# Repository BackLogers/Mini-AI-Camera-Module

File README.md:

# Mini AI Camera Module

## Project Description 

The **Mini AI Camera Module** is a compact platform based on the **ESP32-S3**, combining a standard visible-light camera with a **LiDAR** sensor. The module is designed as a low-cost solution for implementing simple AI algorithms, image recognition, and basic 3D depth perception.

This project includes:
- **OV5640** visible-light camera (5 MP)
- **VL53L5CX** LiDAR camera with an **8×8 pixel** depth map  

*(A future hardware revision is planned to include the **VL53L9CX** sensor featuring a 54×42 pixel resolution.)*

## Key Features

1. **Compact size: 25×25 mm**  
   The module includes mounting holes for easy installation, e.g., in mobile robots.

2. **Two complementary imaging systems**  
   - **OV5640 – 5 MP visible-light camera**  
   - **VL53L5CX – 8×8 pixel LiDAR sensor**

3. **Low production cost**  
   - Uses popular and cost-effective electronic components  
   - PCB designed with simple manufacturing requirements  
   - Complete **JLCPCB** production files included

4. **Ideal for autonomous and IoT projects**  
   Suitable for robotics, autonomous vehicles, perception systems, and IoT devices.

5. **Wireless connectivity**  
   With the ESP32-S3, the module supports:  
   - WiFi  
   - Bluetooth  
   - **ESP-NOW**

6. **Convenient USB and UART interfaces**  
   - Vertical **USB-C** port allows direct mounting to a robot chassis  
   - **SBU1 and SBU2** lines are exposed as **UART**, enabling easy integration with external devices

7. **Easy to use and based on open-source libraries**  
   The project is designed to be simple to integrate and develop with. It relies on well-maintained open-source libraries (including SparkFun drivers) as well as built-in components from the ESP-IDF framework.

8. **Open-source project (Apache 2.0 License)**  
   The entire project is fully open-source and released under the Apache 2.0 license, allowing both personal and commercial use with minimal restrictions.

## Repository Contents

- Technical documentation  
- Schematics and PCB design  
- JLCPCB fabrication files  
- Example firmware for **Arduino**

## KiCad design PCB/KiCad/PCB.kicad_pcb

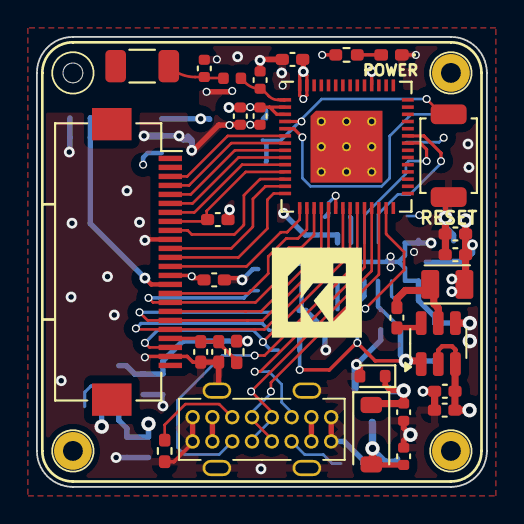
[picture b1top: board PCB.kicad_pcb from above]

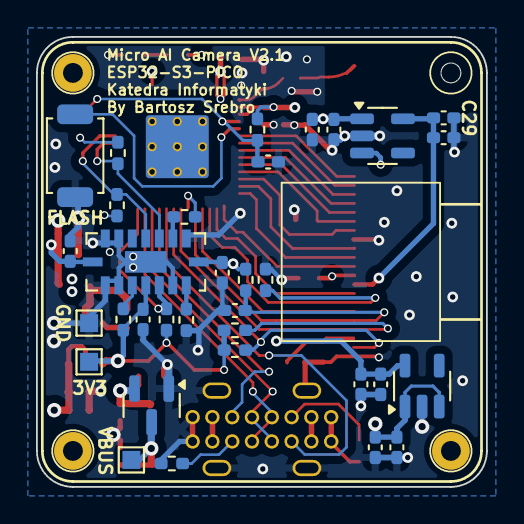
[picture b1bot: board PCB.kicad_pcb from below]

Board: 4 copper layers, 25.0 x 25.0 mm, 67 parts (33 on the bottom side), 42 nets.

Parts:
AE1: Antenna_Ceramic; C_1206_3216Metric
C1: NC; C_0402_1005Metric
C2: 4.7pF; C_0402_1005Metric
C3, C4, C18, C19, C27, C28, C33: 4.7uF; C_0402_1005Metric_Pad0.74x0.62mm_HandSolder
C5, C9, C12, C13, C26, C29, C30, C34, C35, C37: 100nF; C_0402_1005Metric_Pad0.74x0.62mm_HandSolder
C6: 1uF; C_0402_1005Metric
C7, C10: 22uF; C_0402_1005Metric
C8: 100nF; C_0402_1005Metric
C11: 1uF; C_0402_1005Metric_Pad0.74x0.62mm_HandSolder
C15, C21: 10uF; C_0402_1005Metric_Pad0.74x0.62mm_HandSolder
C31, C32: 22uF; C_0402_1005Metric_Pad0.74x0.62mm_HandSolder
C36: 15pF; C_0402_1005Metric_Pad0.74x0.62mm_HandSolder
D1: SBR3U40S1F-7; D_SOD-123
D2: ESD5Z5.0; D_SOD-523
D4: LED; LED_0402_1005Metric_Pad0.77x0.64mm_HandSolder
FB1: 120R-1.3A; R_0402_1005Metric_Pad0.72x0.64mm_HandSolder
H1: MountingHole; MountingHole_1.1mm_M1_No_Pad
H2, H3, H4: MountingHole; MountingHole_1.1mm_M1_DIN965_Pad
J1: USB_C_Vertical; USB_C_Hanbo Electronic MC-118LD-H65
J2: Conn_Camera; Hirose_FH12-24S-0.5SH_1x24-1MP_P0.50mm_Horizontal_WithCamer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
L1: 5.6nH/3.0nH; L_0402_1005Metric
L2: 4.7uF; L_2016
R1, R2, R3, R8: 47k; R_0402_1005Metric_Pad0.72x0.64mm_HandSolder
R4, R5, R10, R11, R15: 4.7k; R_0402_1005Metric_Pad0.72x0.64mm_HandSolder
R6, R7: 5.1k; R_0402_1005Metric_Pad0.72x0.64mm_HandSolder
R9, R12, R13: 10k; R_0402_1005Metric_Pad0.72x0.64mm_HandSolder
SW1: SW_Reset; SW_Push_3.0x4.0mm
SW2: SW_Flash; SW_Push_3.0x4.0mm
TP1: TestPoint_VIN; TestPoint_Pad_1.0x1.0mm
TP2: TestPoint_GND; TestPoint_Pad_1.0x1.0mm
TP3: TestPoint_3V3; TestPoint_Pad_1.0x1.0mm
U1: VL53L5CX-Sensor_Distance; ST_VL53L5CX_HandSoldering
U2: ESP32-S3FH4R2; QFN-56-1EP_7x7mm_P0.4mm_EP4x4mm_ThermalVias_ESP32
U3: CH213K; SOT-23
U5: RT9193-1V2; SOT-23-5
U6: RT9193-2V8; SOT-23-5
U7: AP63203WU; TSOT-23-6

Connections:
+1V2: C27.1, C29.1, J2.10, U5.5 (VOUT)
+2V8: C28.1, C30.1, FB1.1, U6.5 (VOUT)
+3V3: C3.2, C4.1, C5.1, C7.2, C8.1, C9.2, C31.2, C32.2, C35.2, J2.11, L2.2, R1.2, R2.2, R4.2, R5.2, R8.1, R9.1, R10.2, R11.2, R13.1, R15.1, TP3.1, U1.A4 (IOVDD), U1.B1 (AVDD), U1.B7 (AVDD), U2.2 (VDD3P3), U2.3 (VDD3P3), U2.20 (VDD3P3_RTC), U2.46 (VDD3P3_CPU), U2.55 (VDDA), U2.56 (VDDA), U7.1 (FB)
+5V: C10.2, C12.1, C13.1, C15.1, C18.1, C19.1, C21.1, D1.1 (K), D2.1 (K), U3.2 (VO), U5.1 (VIN), U5.3 (EN), U6.1 (VIN), U6.3 (EN), U7.2 (EN), U7.3 (IN)
/AVCC: C33.1, C34.1, FB1.2, J2.4
/CAM_D0: J2.19, U2.9 (GPIO4/ADC1_CH3)
/CAM_D1: J2.21, U2.7 (GPIO2/ADC1_CH1)
/CAM_D2: J2.22, U2.6 (GPIO1/ADC1_CH0)
/CAM_D3: J2.20, U2.8 (GPIO3/ADC1_CH2)
/CAM_D4: J2.18, U2.10 (GPIO5/ADC1_CH4)
/CAM_D5: J2.16, U2.12 (GPIO7/ADC1_CH6)
/CAM_D6: J2.14, U2.13 (GPIO8/ADC1_CH7)
/CAM_D7: J2.12, U2.15 (GPIO10/ADC1_CH9)
/CAM_HSYNC: J2.9, U2.16 (GPIO11/ADC2_CH0)
/CAM_MCLK: J2.13, U2.14 (GPIO9/ADC1_CH8)
/CAM_PCLK: C36.2, J2.17, U2.11 (GPIO6/ADC1_CH5)
/CAM_PWDN: J2.8, R12.1, U2.17 (GPIO12/ADC2_CH1)
/CAM_RST: C37.2, J2.6, R13.2, U2.19 (GPIO14/ADC2_CH3)
/CAM_SCK: J2.5, R10.1, U2.21 (GPIO15/ADC2_CH4/XTAL_32K_P)
/CAM_SDA: J2.3, R11.1, U2.22 (GPIO16/ADC2_CH5/XTAL_32K_N)
/CAM_VSYNC: J2.7, U2.18 (GPIO13/ADC2_CH2)
/D+: J1.A6 (D+), J1.B6 (D+), U2.26 (GPIO20/USB_D+/ADC2_CH9)
/D-: J1.A7 (D-), J1.B7 (D-), U2.25 (GPIO19/USB_D-/ADC2_CH8)
/EN: C11.2, R9.2, SW1.1, U2.4 (CHIP_PU/RESET)
/GPIO0: SW2.1, U2.5 (GPIO0/BOOT)
/SBU1: J1.A8 (SBU1), U2.24 (GPIO18/ADC2_CH7)
/SBU2: J1.B8 (SBU2), U2.23 (GPIO17/ADC2_CH6)
/SCL: R4.1, U1.C4 (SCL), U2.37 (SPICLK_P/GPIO47)
/SDA: R5.1, U1.C3 (SDA), U2.36 (SPICLK_N/GPIO48)
/VL_EN: R2.1, U1.A5 (LPn)
/VL_INT: R1.1, U1.A3 (INT), U2.27 (GPIO21)
/VL_RST: R3.2, U1.A1 (I2C_RST)
GND: C1.1, C2.2, C3.1, C4.2, C5.2, C6.1, C7.1, C8.2, C9.1, C10.1, C11.1, C12.2, C13.2, C15.2, C18.2, C19.2, C21.2, C27.2, C28.2, C29.2, C30.2, C31.1, C32.1, C33.2, C34.2, C35.1, C36.1, C37.1, D2.2 (A), D4.1 (K), J1.A1 (GND), J1.A12 (GND), J1.B1 (GND), J1.B12 (GND), J1.S1 (SHIELD), J2.2, J2.15, R3.1, R6.2, R7.1, R12.2, SW1.2, SW2.2, TP2.1, U1.A2 (RSVD4), U1.A6 (RSVD1), U1.A7 (RSVD2), U1.B4 (T_PAD), U1.C1 (GND), U1.C6 (RSVD3), U1.C7 (GND), U2.57 (GND), U3.1 (GND), U5.2 (GND), U6.2 (GND), U7.4 (GND)
unnamed: AE1.1 (A), C1.2, L1.1
unnamed: D4.2 (A), R15.2
unnamed: J1.A5 (CC1), R6.1
unnamed: J1.B5 (CC2), R7.2
unnamed: R8.2, U1.C2 (RSVD6)
unnamed: C2.1, L1.2, U2.1 (LNA_IN/RF)
unnamed: C26.1, U7.6 (BST)
unnamed: C26.2, L2.1, U7.5 (SW)
VBUS: C6.2, D1.2 (A), J1.A4 (VBUS), J1.A9 (VBUS), J1.B4 (VBUS), J1.B9 (VBUS), TP1.1, U3.3 (VI)

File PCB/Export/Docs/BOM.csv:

"Reference","Value","Datasheet","Footprint","Qty","DNP"
"AE1","Antenna_Ceramic","https://www.mouser.pl/ProductDetail/603-ANT3216LL00R2400","Capacitor_SMD:C_1206_3216Metric","1",""
"C1","NC","~","Capacitor_SMD:C_0402_1005Metric","1",""
"C2","4.7pF","~","Capacitor_SMD:C_0402_1005Metric","1",""
"C3,C4,C18,C19,C27,C28,C33,L2","4.7uF","https://www.mouser.pl/ProductDetail/ABRACON/AOTA-B201610S4R7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,~","Capacitor_SMD:C_0402_1005Metric_Pad0.74x0.62mm_HandSolder,Moje_Footprinty:L_2016","8",""
"C5,C8,C9,C12,C13,C26,C29,C30,C34,C35,C37","100nF","~","Capacitor_SMD:C_0402_1005Metric,Capacitor_SMD:C_0402_1005Metric_Pad0.74x0.62mm_HandSolder","11",""
"C6,C11","1uF","~","Capacitor_SMD:C_0402_1005Metric,Capacitor_SMD:C_0402_1005Metric_Pad0.74x0.62mm_HandSolder","2",""
"C7,C10,C31,C32","22uF","~","Capacitor_SMD:C_0402_1005Metric,Capacitor_SMD:C_0402_1005Metric_Pad0.74x0.62mm_HandSolder","4",""
"C15,C21","10uF","~","Capacitor_SMD:C_0402_1005Metric_Pad0.74x0.62mm_HandSolder","2",""
"C36","15pF","~","Capacitor_SMD:C_0402_1005Metric_Pad0.74x0.62mm_HandSolder","1",""
"D1","SBR3U40S1F-7","http://www.vishay.com/docs/88525/1n5817.pdf","Diode_SMD:D_SOD-123","1",""
"D2","ESD5Z5.0","https://www.onsemi.com/pdf/datasheet/esd5z2.5t1-d.pdf","Diode_SMD:D_SOD-523","1",""
"D4","LED","~","LED_SMD:LED_0402_1005Metric_Pad0.77x0.64mm_HandSolder","1",""
"FB1","120R-1.3A","~","Resistor_SMD:R_0402_1005Metric_Pad0.72x0.64mm_HandSolder","1",""
"H1,H2,H3,H4","MountingHole","~","Moje_Footprinty:MountingHole_1.1mm_M1_DIN965_Pad,Moje_Footprinty:MountingHole_1.1mm_M1_No_Pad","4",""
"J1","USB_C_Vertical","https://www.lcsc.com/product-detail/USB-Connectors_Hanbo-Ele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","Moje_Footprinty:USB_C_Hanbo Electronic MC-118LD-H65","1",""
"J2","Conn_Camera","~","Moje_Footprinty:Hirose_FH12-24S-0.5SH_1x24-1MP_P0.50mm_Horizontal_WithCamera_BackSide_Opt1","1",""
"L1","5.6nH/3.0nH","~","Inductor_SMD:L_0402_1005Metric","1",""
"R1,R2,R3,R8","47k","~","Resistor_SMD:R_0402_1005Metric_Pad0.72x0.64mm_HandSolder","4",""
"R4,R5,R10,R11,R15","4.7k","~","Resistor_SMD:R_0402_1005Metric_Pad0.72x0.64mm_HandSolder","5",""
"R6,R7","5.1k","~","Resistor_SMD:R_0402_1005Metric_Pad0.72x0.64mm_HandSolder","2",""
"R9,R12,R13","10k","~","Resistor_SMD:R_0402_1005Metric_Pad0.72x0.64mm_HandSolder","3",""
"SW1","SW_Reset","~","Moje_Footprinty:SW_Push_3.0x4.0mm","1",""
"SW2","SW_Flash","~","Moje_Footprinty:SW_Push_3.0x4.0mm","1",""
"TP1","TestPoint_VIN","~","TestPoint:TestPoint_Pad_1.0x1.0mm","1",""
"TP2","TestPoint_GND","~","TestPoint:TestPoint_Pad_1.0x1.0mm","1",""
"TP3","TestPoint_3V3","~","TestPoint:TestPoint_Pad_1.0x1.0mm","1",""
"U1","VL53L5CX-Sensor_Distance","","Moje_Footprinty:ST_VL53L5CX_HandSoldering","1",""
"U2","ESP32-S3FH4R2","https://www.espressif.com/sites/default/files/documentation/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","Moje_Footprinty:QFN-56-1EP_7x7mm_P0.4mm_EP4x4mm_ThermalVias_ESP32","1",""
"U3","CH213K","","Package_TO_SOT_SMD:SOT-23","1",""
"U5","RT9193-1V2","","Package_TO_SOT_SMD:SOT-23-5","1",""
"U6","RT9193-2V8","","Package_TO_SOT_SMD:SOT-23-5","1",""
"U7","AP63203WU","https://www.diodes.com/assets/Datasheets/AP63200-AP63201-AP6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","Package_TO_SOT_SMD:TSOT-23-6","1",""

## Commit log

2025-12-01 Project init
2025-12-01 Add Apache License 2.0
    Added the Apache License 2.0 to the project.
2025-12-01 Readme update
